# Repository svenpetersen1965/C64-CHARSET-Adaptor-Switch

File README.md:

# C64-CHARSET-Adaptor-Switch
An Adaptor for the Character ROM of the Commodore C64 (2332 = 4k). It accepts EPROMs of the types 27C64, 27C128, 27C256 and 27C512.

The charcter sets can be selected by jumper or by a microcontroller circuit like an arduino or the keyboard controlled kernal switch: https://github.com/svenpetersen1965/C64-Keyboard-Controlled-Kernal-Switch
# Calculation of the BOM v0.0 prices
The prices were calculated June 9th, 2020. The total costs for the components and PCB are 3.80€, which does not include and shipping fees.

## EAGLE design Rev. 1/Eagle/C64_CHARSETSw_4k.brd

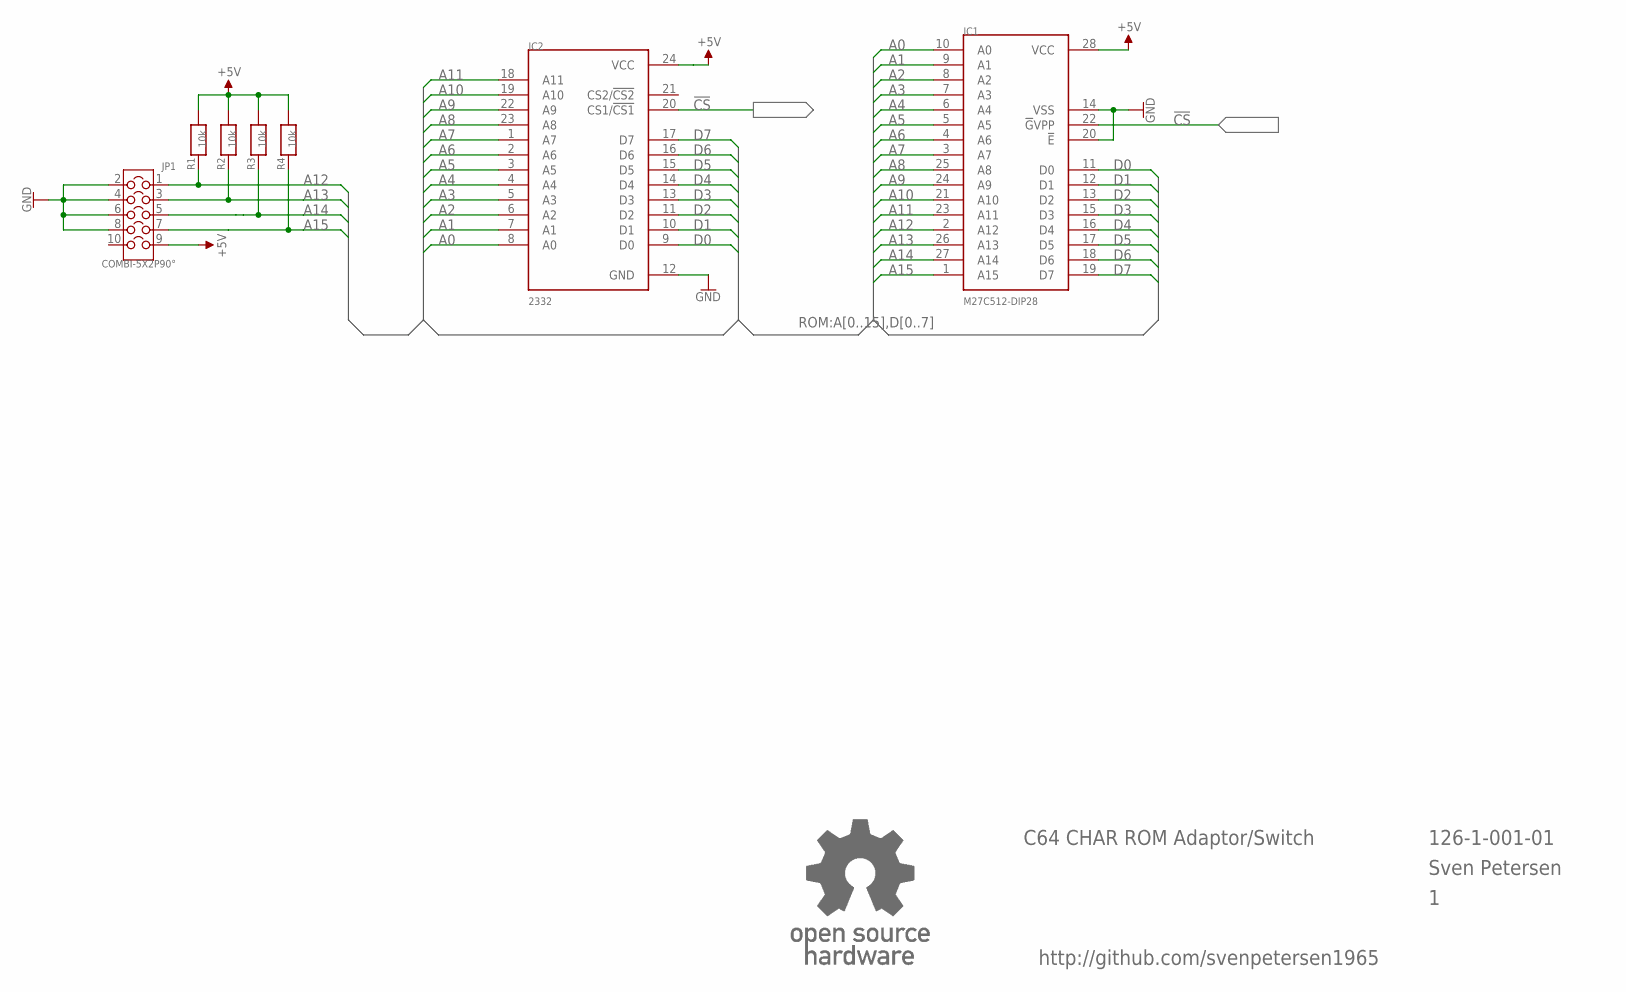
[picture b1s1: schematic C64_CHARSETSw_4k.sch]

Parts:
IC1: M27C512-DIP28; DIL28-6
IC2: 2332; DIL24_SOCKET
JP1: COMBI-5X2P90°; COMBI-5X2-90
R1, R2, R3, R4: 10k; 0805
U$6: OPEN_SOURCE_HW; OPENHW

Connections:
!CS: IC1.22 (!G!VPP), IC2.20 (CS1/!CS1)
+5V: IC1.28 (VCC), IC2.24 (VCC), JP1.9, R1.2, R2.2, R3.2, R4.2
A0: IC1.10 (A0), IC2.8 (A0)
A1: IC1.9 (A1), IC2.7 (A1)
A2: IC1.8 (A2), IC2.6 (A2)
A3: IC1.7 (A3), IC2.5 (A3)
A4: IC1.6 (A4), IC2.4 (A4)
A5: IC1.5 (A5), IC2.3 (A5)
A6: IC1.4 (A6), IC2.2 (A6)
A7: IC1.3 (A7), IC2.1 (A7)
A8: IC1.25 (A8), IC2.23 (A8)
A9: IC1.24 (A9), IC2.22 (A9)
A10: IC1.21 (A10), IC2.19 (A10)
A11: IC1.23 (A11), IC2.18 (A11)
A12: IC1.2 (A12), JP1.1, R1.1
A13: IC1.26 (A13), JP1.3, R2.1
A14: IC1.27 (A14), JP1.5, R3.1
A15: IC1.1 (A15), JP1.7, R4.1
D0: IC1.11 (D0), IC2.9 (D0)
D1: IC1.12 (D1), IC2.10 (D1)
D2: IC1.13 (D2), IC2.11 (D2)
D3: IC1.15 (D3), IC2.13 (D3)
D4: IC1.16 (D4), IC2.14 (D4)
D5: IC1.17 (D5), IC2.15 (D5)
D6: IC1.18 (D6), IC2.16 (D6)
D7: IC1.19 (D7), IC2.17 (D7)
GND: IC1.14 (VSS), IC1.20 (!E), IC2.12 (GND), JP1.2, JP1.4, JP1.6, JP1.8

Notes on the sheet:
126-1-001-01
Sven Petersen
C64 CHAR ROM Adaptor/Switch
http://github.com/svenpetersen1965

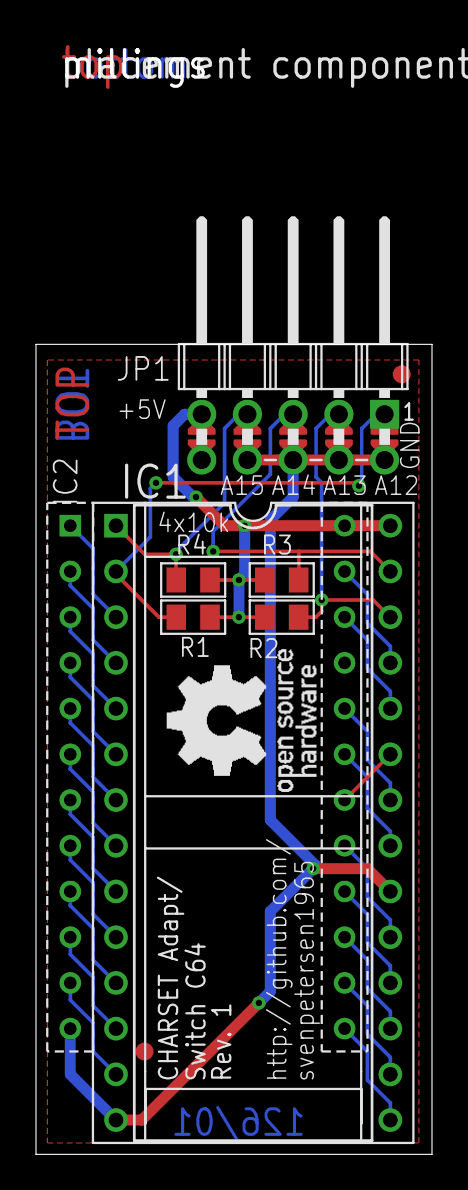
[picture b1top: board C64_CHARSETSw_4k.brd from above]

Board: 2 copper layers, 22.0 x 45.0 mm, 14 parts (1 on the bottom side), 27 nets.

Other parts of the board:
U$11: SVEN_TAG
U$16: GS28P
U$17, U$18: SMD_REF_R1MM
U$19: 2LAYER
U$20: PCB-TITLE/

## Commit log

2020-06-09 Calculation of BOM v0.0
2020-08-07 Silk Screen Revision
2020-08-07 Silk Screen Update
2022-02-25 Rev. 1 released
